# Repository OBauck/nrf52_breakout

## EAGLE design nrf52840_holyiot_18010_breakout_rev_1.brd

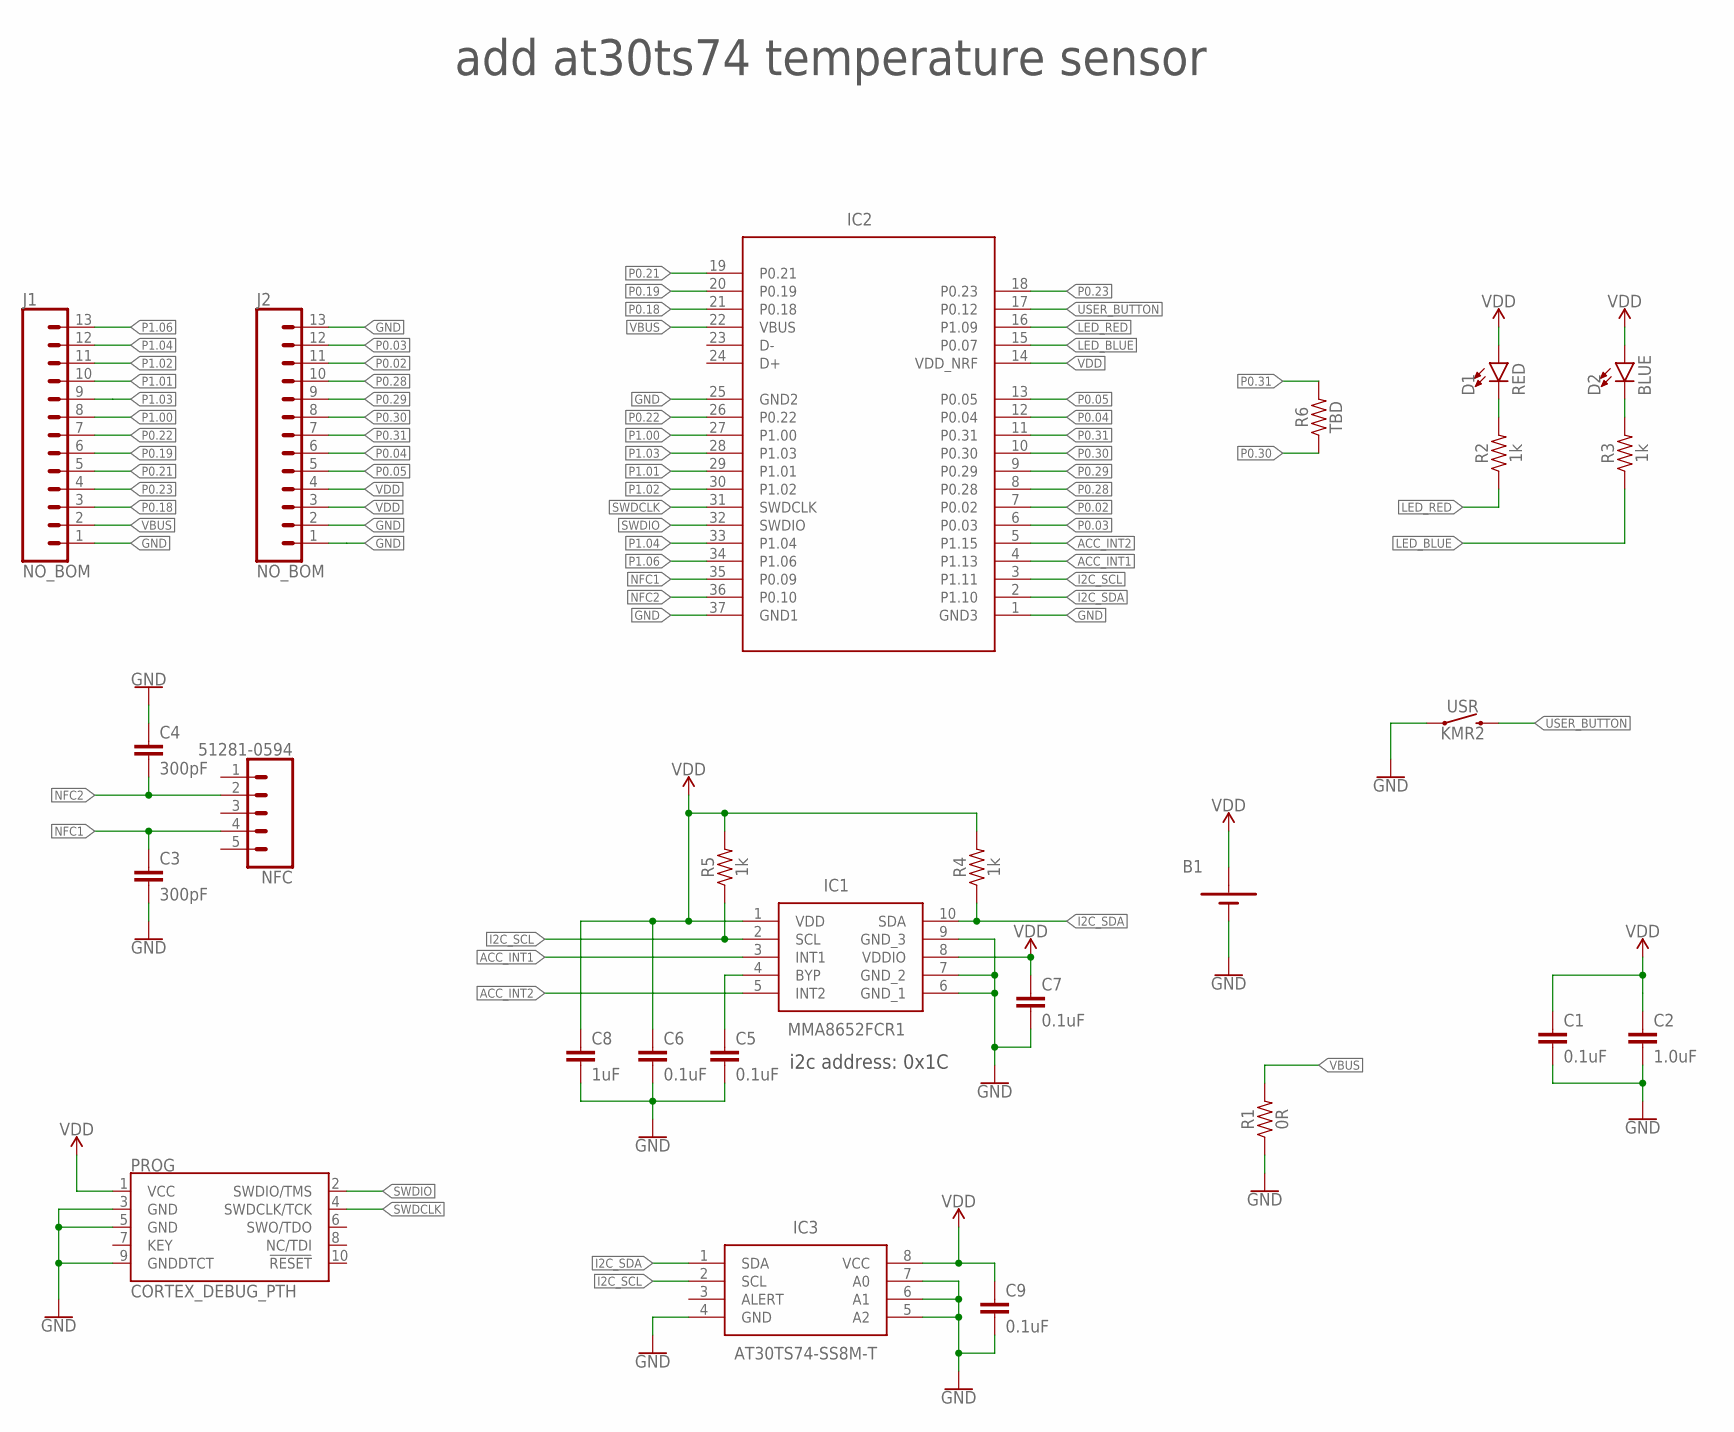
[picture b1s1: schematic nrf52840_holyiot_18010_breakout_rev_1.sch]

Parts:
B1: BATTERY-BU2032; BU2032SM-HD-G
C1, C5, C6, C7, C9: 0.1uF; C0402
C2: 1.0uF; C0603
C3, C4: 300pF; C0402
C8: 1uF; C0402
D1: RED; LED-0603
D2: BLUE; LED-0603
IC1: MMA8652FCR1; SON40P200X200X100-10N
IC2: HOLYIOT_18010; HOLYIOT_18010_REDUCED
IC3: AT30TS74-SS8M-T; SOIC127P600X175-8N
J1, J2: NO_BOM; 1X13_NO_SILK
NFC: 51281-0594
PROG: CORTEX_DEBUG_PTH; 2X5-PTH-1.27MM
R1: 0R; R0402
R2, R3, R4, R5: 1k; R0402
R6: TBD; R0402
USR: KMR2; TACTILE_SWITCH_SMD_4.6X2.8MM

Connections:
ACC_INT1: IC1.3 (INT1), IC2.4 (P1.13)
ACC_INT2: IC1.5 (INT2), IC2.5 (P1.15)
GND: B1.2 (-), C1.2, C2.2, C3.2, C4.1, C5.2, C6.2, C7.2, C8.2, C9.2, IC1.6 (GND_1), IC1.7 (GND_2), IC1.9 (GND_3), IC2.1 (GND3), IC2.25 (GND2), IC2.37 (GND1), IC3.4 (GND), IC3.5 (A2), IC3.6 (A1), IC3.7 (A0), J1.1, J2.1, J2.2, J2.13, PROG.3 (GND), PROG.5 (GND), PROG.9 (GNDDTCT), R1.1, USR.1, USR.2 (1)
I2C_SCL: IC1.2 (SCL), IC2.3 (P1.11), IC3.2 (SCL), R5.1
I2C_SDA: IC1.10 (SDA), IC2.2 (P1.10), IC3.1 (SDA), R4.1
LED_BLUE: IC2.15 (P0.07), R3.1
LED_RED: IC2.16 (P1.09), R2.1
unnamed: D1.C, R2.2
unnamed: D2.C, R3.2
unnamed: C5.1, IC1.4 (BYP)
NFC1: C3.1, IC2.35 (P0.09), NFC.4
NFC2: C4.2, IC2.36 (P0.10), NFC.2
P0.02: IC2.7 (P0.02), J2.11
P0.03: IC2.6 (P0.03), J2.12
P0.04: IC2.12 (P0.04), J2.6
P0.05: IC2.13 (P0.05), J2.5
P0.18: IC2.21 (P0.18), J1.3
P0.19: IC2.20 (P0.19), J1.6
P0.21: IC2.19 (P0.21), J1.5
P0.22: IC2.26 (P0.22), J1.7
P0.23: IC2.18 (P0.23), J1.4
P0.28: IC2.8 (P0.28), J2.10
P0.29: IC2.9 (P0.29), J2.9
P0.30: IC2.10 (P0.30), J2.8, R6.1
P0.31: IC2.11 (P0.31), J2.7, R6.2
P1.00: IC2.27 (P1.00), J1.8
P1.01: IC2.29 (P1.01), J1.10
P1.02: IC2.30 (P1.02), J1.11
P1.03: IC2.28 (P1.03), J1.9
P1.04: IC2.33 (P1.04), J1.12
P1.06: IC2.34 (P1.06), J1.13
SWDCLK: IC2.31 (SWDCLK), PROG.4 (SWDCLK/TCK)
SWDIO: IC2.32 (SWDIO), PROG.2 (SWDIO/TMS)
USER_BUTTON: IC2.17 (P0.12), USR.3 (2), USR.4 (2)
VBUS: IC2.22 (VBUS), J1.2, R1.2
VDD: B1.1 (+), C1.1, C2.1, C6.1, C7.1, C8.1, C9.1, D1.A, D2.A, IC1.1 (VDD), IC1.8 (VDDIO), IC2.14 (VDD_NRF), IC3.8 (VCC), J2.3, J2.4, PROG.1 (VCC), R4.2, R5.2

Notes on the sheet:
i2c address: 0x1C
add at30ts74 temperature sensor

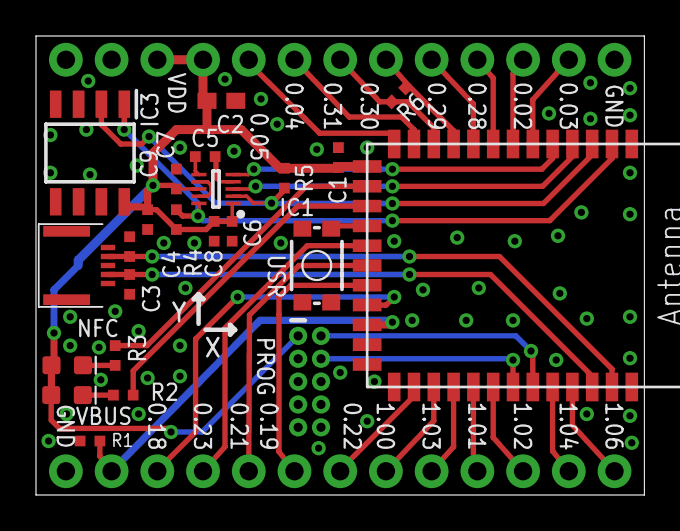
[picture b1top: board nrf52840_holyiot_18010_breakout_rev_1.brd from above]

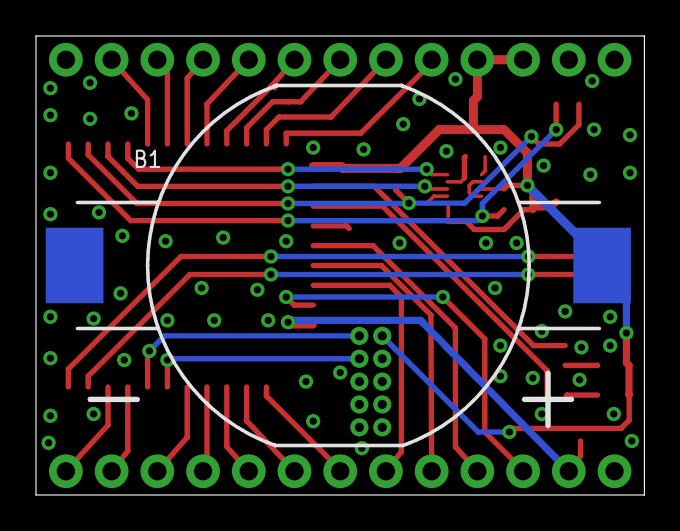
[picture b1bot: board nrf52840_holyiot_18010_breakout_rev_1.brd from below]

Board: 2 copper layers, 33.8 x 25.5 mm, 26 parts (3 on the bottom side), 36 nets.

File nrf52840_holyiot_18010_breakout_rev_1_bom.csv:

Design title:;nrf52840_holyiot_18010_breakout_rev_1;;;;;
Date:;31.10.2018 18.40;;;;;
Designer:;Ole Bauck;;;;;
Company:;Inventas;;;;;
;;;;;;
Item;Qty;Refdes;Description;Value;MANUFACTURER_PART_NUMBER;MANUFACTURER_NAME
1;5;C1, C5, C6, C7, C9;CAP-6.3V-20%-0402;0.1uF;;
2;1;R1;RES-0.063W-5%-0402;0R;;
3;1;C2;CAP-6.3V-20%-0603;1.0uF;;
4;4;R2, R3, R4, R5;RES-0.063W-5%-0402;1k;;
5;1;C8;CAP-6.3V-20%-0402;1uF;;
6;2;C3, C4;CAP-6.3V-20%-0402;300pF;;
7;1;NFC;51281-0594;51281-0594;51281-0594;Molex
8;1;IC3;AT30TS74-SS8M-T;AT30TS74-SS8M-T;AT30TS74-SS8M-T;microchip
9;1;B1;BATTERY-BU2032;BATTERY-BU2032;BU2032SM-HD-G;MPD
10;1;D2;LED0603;BLUE;;
11;1;PROG;CORTEX_DEBUG_PTH;CORTEX_DEBUG_PTH;;
12;1;IC2;HOLYIOT_18010;HOLYIOT_18010;18010;Holyiot
13;1;USR;KMR2;KMR2;KMR211GLFS;C&K
14;1;IC1;MMA8652FCR1;MMA8652FCR1;MMA8652FCR1;NXP
15;1;D1;LED0603;RED;;
16;1;R6;RES-0.063W-1%-0402;TBD;;
;;;;;;
The following components shall not be mounted;;;;;;
Item;Qty;Refdes;Description;Value;MANUFACTURER_PART_NUMBER;MANUFACTURER_NAME

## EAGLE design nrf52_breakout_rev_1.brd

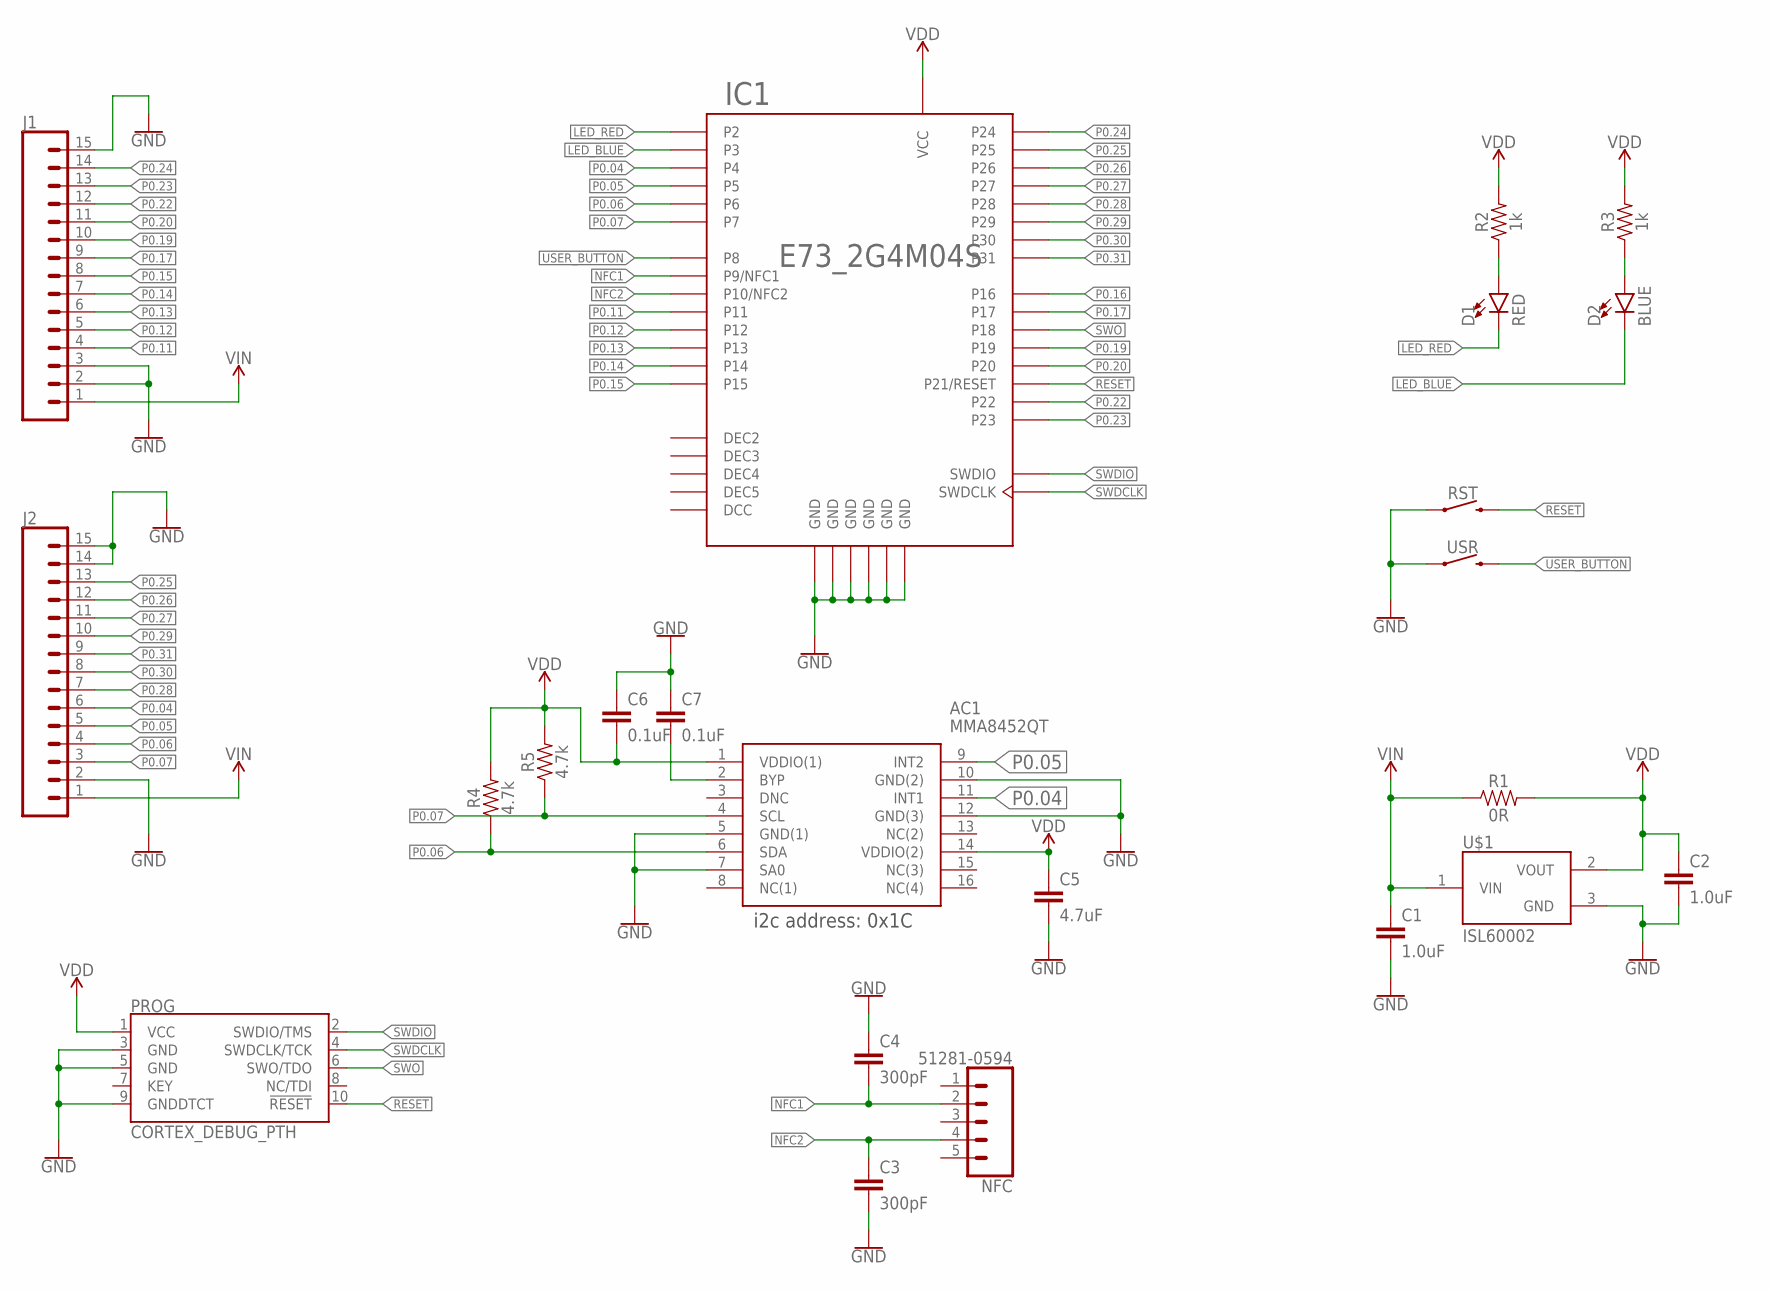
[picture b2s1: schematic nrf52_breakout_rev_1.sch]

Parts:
AC1: MMA8452QT; PQFN50P300X300X100-16N
C1, C2: 1.0uF; 0603
C3, C4: 300pF; 0402
C5: 4.7uF; 0603
C6, C7: 0.1uF; 0402
D1: RED; LED-0603
D2: BLUE; LED-0603
IC1: E73_2G4M04S
J1, J2: CONN_15; 1X15
NFC: 51281-0594
PROG: CORTEX_DEBUG_PTH; 2X5-PTH-1.27MM
R1: 0R; 0603
R2, R3: 1k; 0603
R4, R5: 4.7k; 0402
RST: MOMENTARY-SWITCH-SPST-SMD-4.6X2.8MM; TACTILE_SWITCH_SMD_4.6X2.8MM
U$1: ISL60002; SOT23-3
USR: MOMENTARY-SWITCH-SPST-SMD-4.6X2.8MM; TACTILE_SWITCH_SMD_4.6X2.8MM

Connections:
DCC: IC1.13 (DCC)
DEC2: IC1.3 (DEC2)
DEC3: IC1.4 (DEC3)
DEC4: IC1.12 (DEC4)
DEC5: IC1.14 (DEC5)
GND: AC1.5 (GND(1)), AC1.7 (SA0), AC1.10 (GND(2)), AC1.12 (GND(3)), C1.2, C2.2, C3.2, C4.1, C5.2, C6.1, C7.1, IC1.0 (GND), IC1.1 (GND), IC1.2 (GND), IC1.15 (GND), IC1.42 (GND), IC1.43 (GND), J1.2, J1.3, J1.15, J2.2, J2.14, J2.15, PROG.3 (GND), PROG.5 (GND), PROG.9 (GNDDTCT), RST.1, RST.2 (1), U$1.3 (GND), USR.1, USR.2 (1)
LED_BLUE: D2.C, IC1.18 (P3)
LED_RED: D1.C, IC1.17 (P2)
unnamed: D2.A, R3.1
unnamed: D1.A, R2.1
unnamed: AC1.2 (BYP), C7.2
NFC1: C4.2, IC1.24 (P9/NFC1), NFC.2
NFC2: C3.1, IC1.25 (P10/NFC2), NFC.4
P0.04: AC1.11 (INT1), IC1.19 (P4), J2.6
P0.05: AC1.9 (INT2), IC1.20 (P5), J2.5
P0.06: AC1.6 (SDA), IC1.21 (P6), J2.4, R4.1
P0.07: AC1.4 (SCL), IC1.22 (P7), J2.3, R5.1
P0.11: IC1.26 (P11), J1.4
P0.12: IC1.27 (P12), J1.5
P0.13: IC1.28 (P13), J1.6
P0.14: IC1.29 (P14), J1.7
P0.15: IC1.30 (P15), J1.8
P0.16: IC1.31 (P16)
P0.17: IC1.32 (P17), J1.9
P0.19: IC1.34 (P19), J1.10
P0.20: IC1.35 (P20), J1.11
P0.22: IC1.39 (P22), J1.12
P0.23: IC1.40 (P23), J1.13
P0.24: IC1.41 (P24), J1.14
P0.25: IC1.5 (P25), J2.13
P0.26: IC1.6 (P26), J2.12
P0.27: IC1.7 (P27), J2.11
P0.28: IC1.8 (P28), J2.7
P0.29: IC1.9 (P29), J2.10
P0.30: IC1.10 (P30), J2.8
P0.31: IC1.11 (P31), J2.9
RESET: IC1.36 (P21/RESET), PROG.10 (!RESET), RST.3 (2), RST.4 (2)
SWDCLK: IC1.37 (SWDCLK), PROG.4 (SWDCLK/TCK)
SWDIO: IC1.38 (SWDIO), PROG.2 (SWDIO/TMS)
SWO: IC1.33 (P18), PROG.6 (SWO/TDO)
USER_BUTTON: IC1.23 (P8), USR.3 (2), USR.4 (2)
VDD: AC1.1 (VDDIO(1)), AC1.14 (VDDIO(2)), C2.1, C5.1, C6.2, IC1.16 (VCC), PROG.1 (VCC), R1.2, R2.2, R3.2, R4.2, R5.2, U$1.2 (VOUT)
VIN: C1.1, J1.1, J2.1, R1.1, U$1.1 (VIN)

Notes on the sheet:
i2c address: 0x1C

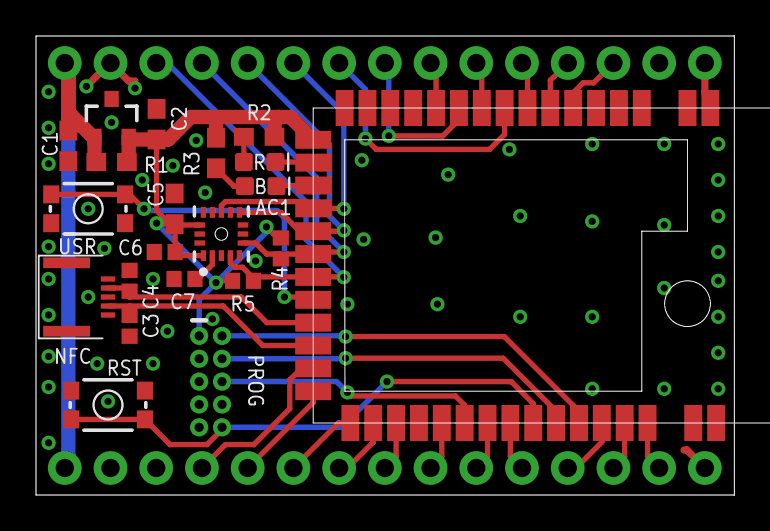
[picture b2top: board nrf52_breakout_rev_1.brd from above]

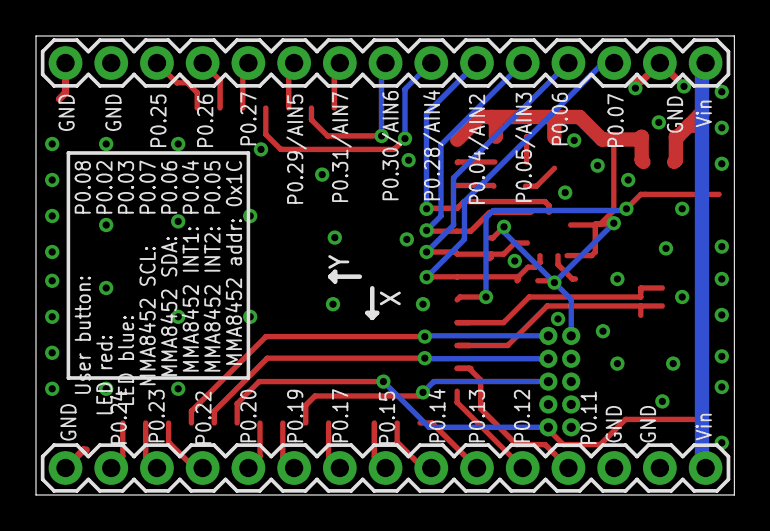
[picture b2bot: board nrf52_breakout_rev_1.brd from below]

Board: 2 copper layers, 38.8 x 25.5 mm, 23 parts (2 on the bottom side), 37 nets.

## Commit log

2018-02-17 ready for order
2018-02-18 added some stuff to the silkscreen
2018-10-08 added todo list
2018-10-09 added project for laird nrf52832 module and holyiot nrf52840 module
2018-10-10 added temp sensor, first draft routing done
2018-10-13 added 3D files
2018-10-13 small fixes when adding 3D packages

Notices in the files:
parts and their libraries:
SparkFun-Aesthetics: Licensing: Creative Commons ShareAlike 4.0 International - https://creativecommons.org/licenses/by-sa/4.0
